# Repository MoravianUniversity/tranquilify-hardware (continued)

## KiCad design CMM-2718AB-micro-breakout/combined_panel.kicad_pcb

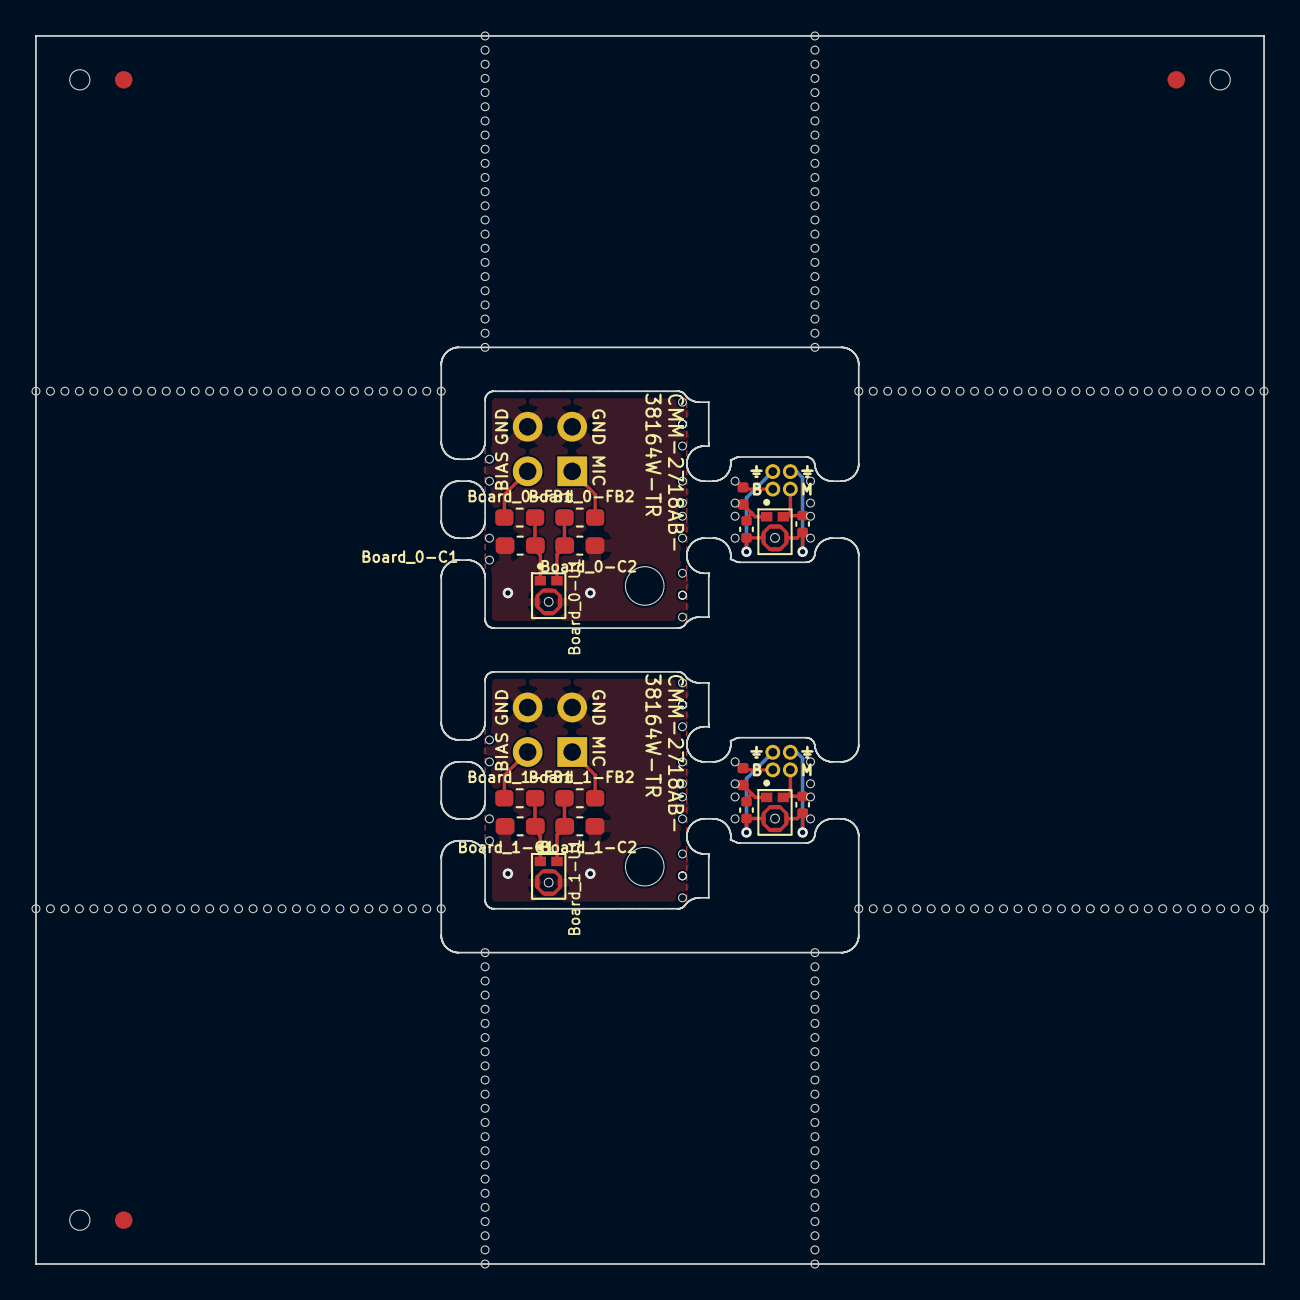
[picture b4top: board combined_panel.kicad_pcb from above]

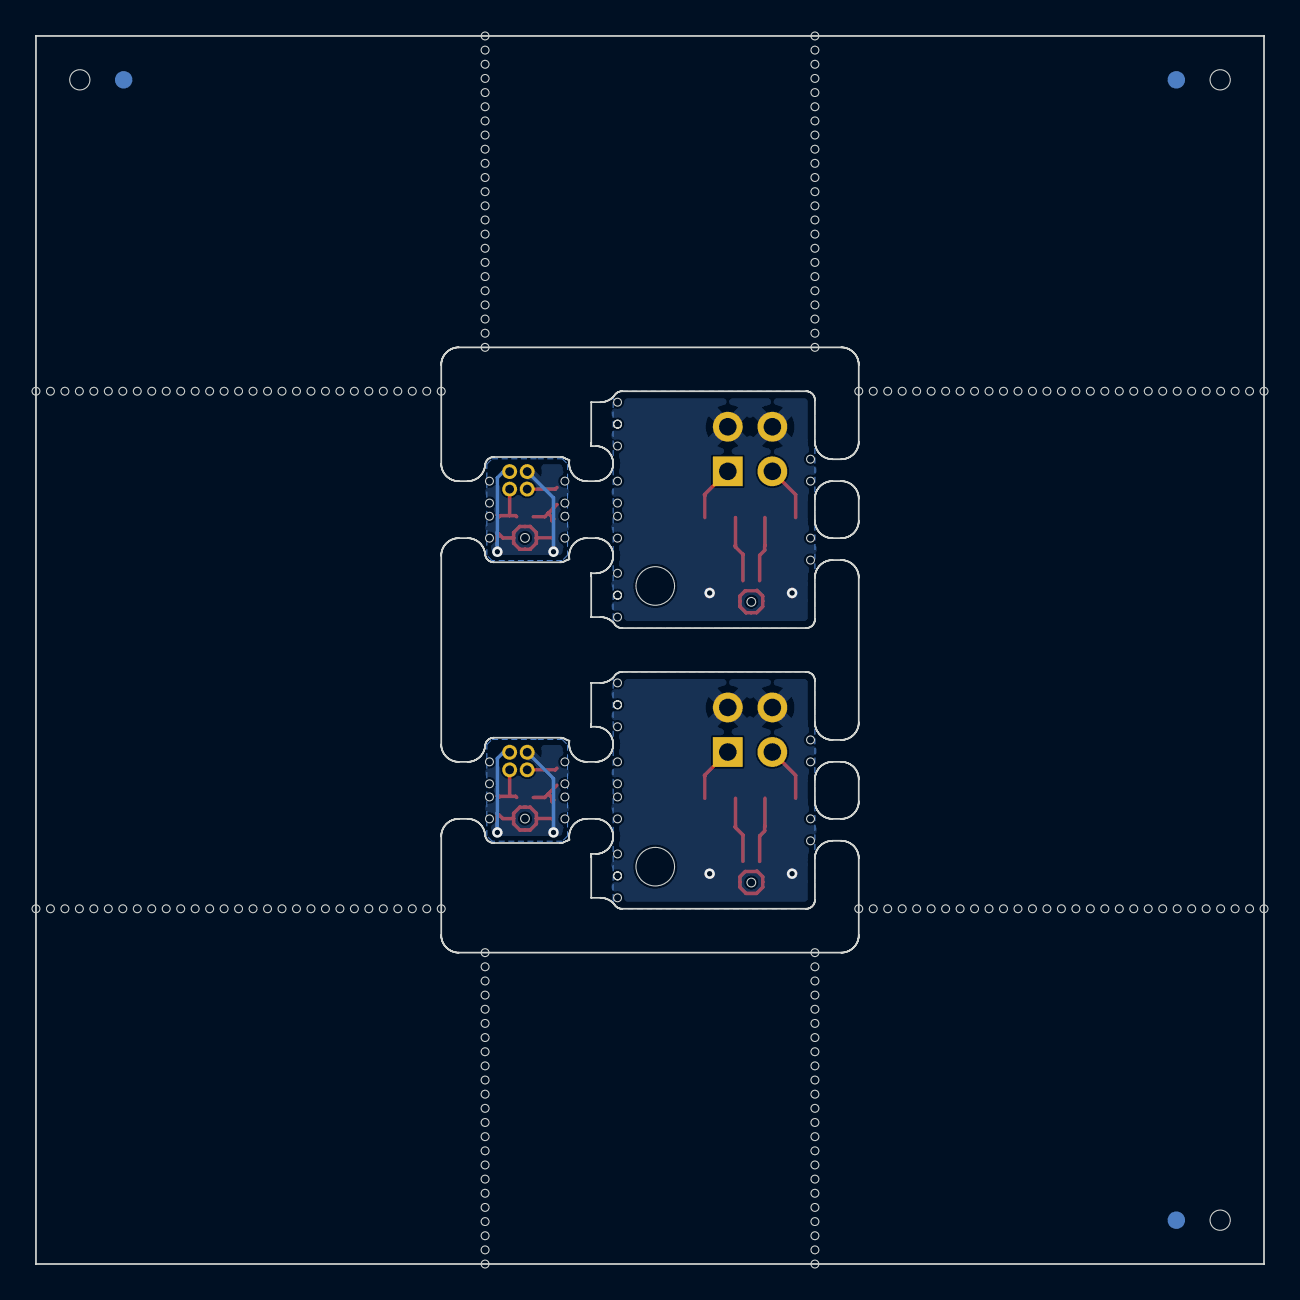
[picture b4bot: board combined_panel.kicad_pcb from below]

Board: 2 copper layers, 70.0 x 70.0 mm, 289 parts (3 on the bottom side), 18 nets.

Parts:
Board_0-C1, Board_1-C1: 100nF; C_0603_1608Metric_Pad1.08x0.95mm_HandSolder
Board_0-C2, Board_1-C2: 15pF; C_0603_1608Metric_Pad1.08x0.95mm_HandSolder
Board_0-FB1, Board_0-FB2, Board_1-FB1, Board_1-FB2: BLM18AG102SN1D; L_0603_1608Metric_Pad1.05x0.95mm_HandSolder
Board_0-H1, Board_1-H1: MountingHole_2.2mm_M2
Board_0-J1, Board_1-J1: Conn_02x02; PinHeader_2x02_P2.54mm_Vertical
Board_0-U1, Board_1-U1, Board_2-U1, Board_3-U1: CMM-2718AB-38164W-TR
Board_2-C1, Board_3-C1: 100nF; C_0402_1005Metric
Board_2-C2, Board_3-C2: 15pF; C_0402_1005Metric
Board_2-FB1, Board_3-FB1: BLM15AG102SN1D; L_0402_1005Metric
Board_2-J1, Board_3-J1: Conn; PinHeader_2x02_P1.00mm_Vertical
KiKit_FID_B_1, KiKit_FID_B_2, KiKit_FID_B_3: Fiducial
KiKit_FID_T_1, KiKit_FID_T_2, KiKit_FID_T_3: Fiducial
KiKit_MB_1_1, KiKit_MB_1_2, KiKit_MB_2_1, KiKit_MB_2_2, KiKit_MB_3_1, KiKit_MB_3_2, KiKit_MB_4_1, KiKit_MB_4_2, KiKit_MB_5_1, KiKit_MB_5_2, KiKit_MB_6_1, KiKit_MB_6_2, KiKit_MB_7_1, KiKit_MB_7_2, KiKit_MB_8_1, KiKit_MB_8_2, KiKit_MB_9_1, KiKit_MB_9_2, KiKit_MB_10_1, KiKit_MB_10_2, KiKit_MB_11_1, KiKit_MB_11_2, KiKit_MB_12_1, KiKit_MB_12_2, KiKit_MB_13_1, KiKit_MB_13_2, KiKit_MB_14_1, KiKit_MB_14_2, KiKit_MB_15_1, KiKit_MB_15_2, KiKit_MB_16_1, KiKit_MB_16_2, KiKit_MB_17_1, KiKit_MB_17_2, KiKit_MB_18_1, KiKit_MB_18_2, KiKit_MB_19_1, KiKit_MB_19_2, KiKit_MB_20_1, KiKit_MB_20_2, KiKit_MB_21_1, KiKit_MB_21_2, KiKit_MB_22_1, KiKit_MB_22_2, KiKit_MB_23_1, KiKit_MB_23_2, KiKit_MB_24_1, KiKit_MB_24_2, KiKit_MB_25_1, KiKit_MB_25_2, KiKit_MB_25_3, KiKit_MB_25_4, KiKit_MB_25_5, KiKit_MB_25_6, KiKit_MB_25_7, KiKit_MB_25_8, KiKit_MB_25_9, KiKit_MB_25_10, KiKit_MB_25_11, KiKit_MB_25_12, KiKit_MB_25_13, KiKit_MB_25_14, KiKit_MB_25_15, KiKit_MB_25_16, KiKit_MB_25_17, KiKit_MB_25_18, KiKit_MB_25_19, KiKit_MB_25_20, KiKit_MB_25_21, KiKit_MB_25_22, KiKit_MB_25_23, KiKit_MB_26_1, KiKit_MB_26_2, KiKit_MB_26_3, KiKit_MB_26_4, KiKit_MB_26_5, KiKit_MB_26_6, KiKit_MB_26_7, KiKit_MB_26_8, KiKit_MB_26_9, KiKit_MB_26_10, KiKit_MB_26_11, KiKit_MB_26_12, KiKit_MB_26_13, KiKit_MB_26_14, KiKit_MB_26_15, KiKit_MB_26_16, KiKit_MB_26_17, KiKit_MB_26_18, KiKit_MB_26_19, KiKit_MB_26_20, KiKit_MB_26_21, KiKit_MB_26_22, KiKit_MB_26_23, KiKit_MB_27_1, KiKit_MB_27_2, KiKit_MB_27_3, KiKit_MB_27_4, KiKit_MB_27_5, KiKit_MB_27_6, KiKit_MB_27_7, KiKit_MB_27_8, KiKit_MB_27_9, KiKit_MB_27_10, KiKit_MB_27_11, KiKit_MB_27_12, KiKit_MB_27_13, KiKit_MB_27_14, KiKit_MB_27_15, KiKit_MB_27_16, KiKit_MB_27_17, KiKit_MB_27_18, KiKit_MB_27_19, KiKit_MB_27_20, KiKit_MB_27_21, KiKit_MB_27_22, KiKit_MB_27_23, KiKit_MB_28_1, KiKit_MB_28_2, KiKit_MB_28_3, KiKit_MB_28_4, KiKit_MB_28_5, KiKit_MB_28_6, KiKit_MB_28_7, KiKit_MB_28_8, KiKit_MB_28_9, KiKit_MB_28_10, KiKit_MB_28_11, KiKit_MB_28_12, KiKit_MB_28_13, KiKit_MB_28_14, KiKit_MB_28_15, KiKit_MB_28_16, KiKit_MB_28_17, KiKit_MB_28_18, KiKit_MB_28_19, KiKit_MB_28_20, KiKit_MB_28_21, KiKit_MB_28_22, KiKit_MB_28_23, KiKit_MB_29_1, KiKit_MB_29_2, KiKit_MB_29_3, KiKit_MB_29_4, KiKit_MB_29_5, KiKit_MB_29_6, KiKit_MB_29_7, KiKit_MB_29_8, KiKit_MB_29_9, KiKit_MB_29_10, KiKit_MB_29_11, KiKit_MB_29_12, KiKit_MB_29_13, KiKit_MB_29_14, KiKit_MB_29_15, KiKit_MB_29_16, KiKit_MB_29_17, KiKit_MB_29_18, KiKit_MB_29_19, KiKit_MB_29_20, KiKit_MB_29_21, KiKit_MB_29_22, KiKit_MB_29_23, KiKit_MB_29_24, KiKit_MB_29_25, KiKit_MB_29_26, KiKit_MB_29_27, KiKit_MB_29_28, KiKit_MB_29_29, KiKit_MB_30_1, KiKit_MB_30_2, KiKit_MB_30_3, KiKit_MB_30_4, KiKit_MB_30_5, KiKit_MB_30_6, KiKit_MB_30_7, KiKit_MB_30_8, KiKit_MB_30_9, KiKit_MB_30_10, KiKit_MB_30_11, KiKit_MB_30_12, KiKit_MB_30_13, KiKit_MB_30_14, KiKit_MB_30_15, KiKit_MB_30_16, KiKit_MB_30_17, KiKit_MB_30_18, KiKit_MB_30_19, KiKit_MB_30_20, KiKit_MB_30_21, KiKit_MB_30_22, KiKit_MB_30_23, KiKit_MB_30_24, KiKit_MB_30_25, KiKit_MB_30_26, KiKit_MB_30_27, KiKit_MB_30_28, KiKit_MB_30_29, KiKit_MB_31_1, KiKit_MB_31_2, KiKit_MB_31_3, KiKit_MB_31_4, KiKit_MB_31_5, KiKit_MB_31_6, KiKit_MB_31_7, KiKit_MB_31_8, KiKit_MB_31_9, KiKit_MB_31_10, KiKit_MB_31_11, KiKit_MB_31_12, KiKit_MB_31_13, KiKit_MB_31_14, KiKit_MB_31_15, KiKit_MB_31_16, KiKit_MB_31_17, KiKit_MB_31_18, KiKit_MB_31_19, KiKit_MB_31_20, KiKit_MB_31_21, KiKit_MB_31_22, KiKit_MB_31_23, KiKit_MB_31_24, KiKit_MB_31_25, KiKit_MB_31_26, KiKit_MB_31_27, KiKit_MB_31_28, KiKit_MB_31_29, KiKit_MB_32_1, KiKit_MB_32_2, KiKit_MB_32_3, KiKit_MB_32_4, KiKit_MB_32_5, KiKit_MB_32_6, KiKit_MB_32_7, KiKit_MB_32_8, KiKit_MB_32_9, KiKit_MB_32_10, KiKit_MB_32_11, KiKit_MB_32_12, KiKit_MB_32_13, KiKit_MB_32_14, KiKit_MB_32_15, KiKit_MB_32_16, KiKit_MB_32_17, KiKit_MB_32_18, KiKit_MB_32_19, KiKit_MB_32_20, KiKit_MB_32_21, KiKit_MB_32_22, KiKit_MB_32_23, KiKit_MB_32_24, KiKit_MB_32_25, KiKit_MB_32_26, KiKit_MB_32_27, KiKit_MB_32_28, KiKit_MB_32_29: NPTH
KiKit_TO_1, KiKit_TO_2, KiKit_TO_3: NPTH

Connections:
Board_0-/BIAS: Board_0-FB1.1, Board_0-J1.3
Board_0-/OUT: Board_0-FB2.2, Board_0-J1.4
Board_0-/VDD: Board_0-C1.1, Board_0-FB1.2, Board_0-U1.1 (VDD)
Board_0-GND: Board_0-C1.2, Board_0-C2.2, Board_0-J1.1, Board_0-J1.2, Board_0-U1.3 (GND)
Board_0-Net-(U1-OUT): Board_0-C2.1, Board_0-FB2.1, Board_0-U1.2 (OUT)
Board_1-/BIAS: Board_1-FB1.1, Board_1-J1.3
Board_1-/OUT: Board_1-FB2.2, Board_1-J1.4
Board_1-/VDD: Board_1-C1.1, Board_1-FB1.2, Board_1-U1.1 (VDD)
Board_1-GND: Board_1-C1.2, Board_1-C2.2, Board_1-J1.1, Board_1-J1.2, Board_1-U1.3 (GND)
Board_1-Net-(U1-OUT): Board_1-C2.1, Board_1-FB2.1, Board_1-U1.2 (OUT)
Board_2-/BIAS: Board_2-FB1.1, Board_2-J1.3
Board_2-/OUT: Board_2-C2.1, Board_2-J1.4, Board_2-U1.2 (OUT)
Board_2-/VDD: Board_2-C1.1, Board_2-FB1.2, Board_2-U1.1 (VDD)
Board_2-GND: Board_2-C1.2, Board_2-C2.2, Board_2-J1.1, Board_2-J1.2, Board_2-U1.3 (GND)
Board_3-/BIAS: Board_3-FB1.1, Board_3-J1.3
Board_3-/OUT: Board_3-C2.1, Board_3-J1.4, Board_3-U1.2 (OUT)
Board_3-/VDD: Board_3-C1.1, Board_3-FB1.2, Board_3-U1.1 (VDD)
Board_3-GND: Board_3-C1.2, Board_3-C2.2, Board_3-J1.1, Board_3-J1.2, Board_3-U1.3 (GND)

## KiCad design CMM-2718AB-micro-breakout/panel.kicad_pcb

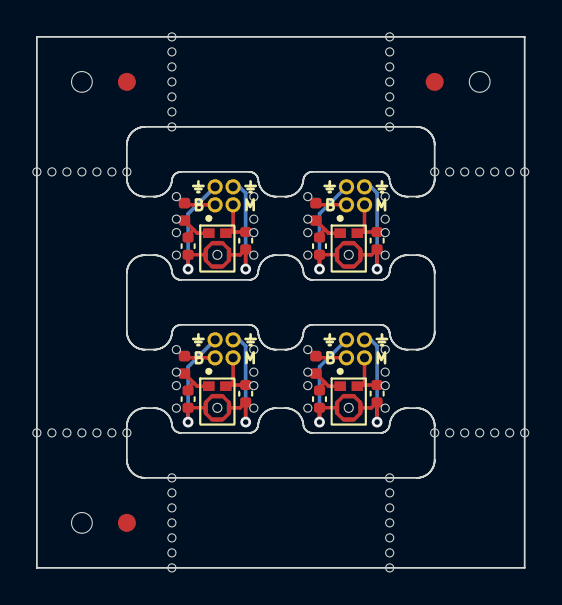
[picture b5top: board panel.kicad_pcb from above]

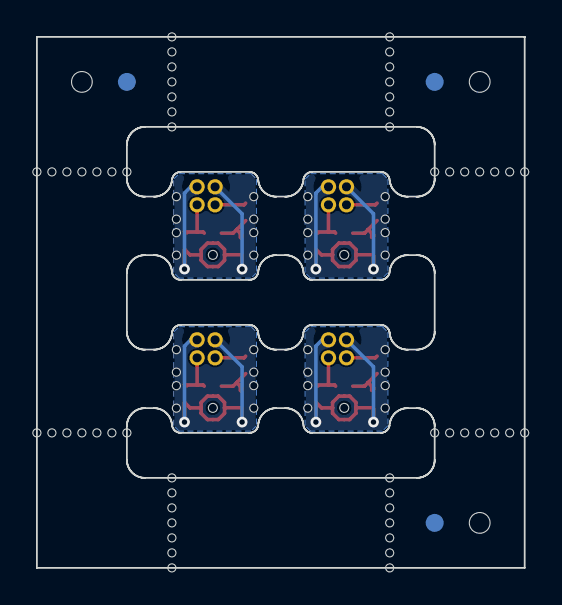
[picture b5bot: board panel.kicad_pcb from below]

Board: 2 copper layers, 27.1 x 29.5 mm, 117 parts (3 on the bottom side), 16 nets.

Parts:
C1, C1#2, C1#3, C1#4: 100nF; C_0402_1005Metric
C2, C2#2, C2#3, C2#4: 15pF; C_0402_1005Metric
FB1, FB1#2, FB1#3, FB1#4: BLM15AG102SN1D; L_0402_1005Metric
J1, J1#2, J1#3, J1#4: Conn; PinHeader_2x02_P1.00mm_Vertical
KiKit_FID_B_1, KiKit_FID_B_2, KiKit_FID_B_3: Fiducial
KiKit_FID_T_1, KiKit_FID_T_2, KiKit_FID_T_3: Fiducial
KiKit_MB_1_1, KiKit_MB_1_2, KiKit_MB_2_1, KiKit_MB_2_2, KiKit_MB_3_1, KiKit_MB_3_2, KiKit_MB_4_1, KiKit_MB_4_2, KiKit_MB_5_1, KiKit_MB_5_2, KiKit_MB_6_1, KiKit_MB_6_2, KiKit_MB_7_1, KiKit_MB_7_2, KiKit_MB_8_1, KiKit_MB_8_2, KiKit_MB_9_1, KiKit_MB_9_2, KiKit_MB_10_1, KiKit_MB_10_2, KiKit_MB_11_1, KiKit_MB_11_2, KiKit_MB_12_1, KiKit_MB_12_2, KiKit_MB_13_1, KiKit_MB_13_2, KiKit_MB_14_1, KiKit_MB_14_2, KiKit_MB_15_1, KiKit_MB_15_2, KiKit_MB_16_1, KiKit_MB_16_2, KiKit_MB_17_1, KiKit_MB_17_2, KiKit_MB_17_3, KiKit_MB_17_4, KiKit_MB_17_5, KiKit_MB_17_6, KiKit_MB_17_7, KiKit_MB_18_1, KiKit_MB_18_2, KiKit_MB_18_3, KiKit_MB_18_4, KiKit_MB_18_5, KiKit_MB_18_6, KiKit_MB_18_7, KiKit_MB_19_1, KiKit_MB_19_2, KiKit_MB_19_3, KiKit_MB_19_4, KiKit_MB_19_5, KiKit_MB_19_6, KiKit_MB_19_7, KiKit_MB_20_1, KiKit_MB_20_2, KiKit_MB_20_3, KiKit_MB_20_4, KiKit_MB_20_5, KiKit_MB_20_6, KiKit_MB_20_7, KiKit_MB_21_1, KiKit_MB_21_2, KiKit_MB_21_3, KiKit_MB_21_4, KiKit_MB_21_5, KiKit_MB_21_6, KiKit_MB_21_7, KiKit_MB_22_1, KiKit_MB_22_2, KiKit_MB_22_3, KiKit_MB_22_4, KiKit_MB_22_5, KiKit_MB_22_6, KiKit_MB_22_7, KiKit_MB_23_1, KiKit_MB_23_2, KiKit_MB_23_3, KiKit_MB_23_4, KiKit_MB_23_5, KiKit_MB_23_6, KiKit_MB_23_7, KiKit_MB_24_1, KiKit_MB_24_2, KiKit_MB_24_3, KiKit_MB_24_4, KiKit_MB_24_5, KiKit_MB_24_6, KiKit_MB_24_7: NPTH
KiKit_TO_1, KiKit_TO_2, KiKit_TO_3: NPTH
U1, U1#2, U1#3, U1#4: CMM-2718AB-38164W-TR

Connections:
Board_0-/BIAS: FB1#3.1, J1.3
Board_0-/OUT: C2#2.1, J1.4, U1.2 (OUT)
Board_0-/VDD: C1#2.1, FB1#3.2, U1.1 (VDD)
Board_0-GND: C1#2.2, C2#2.2, J1.1, J1.2, U1.3 (GND)
Board_1-/BIAS: FB1.1, J1#2.3
Board_1-/OUT: C2#4.1, J1#2.4, U1#4.2 (OUT)
Board_1-/VDD: C1#4.1, FB1.2, U1#4.1 (VDD)
Board_1-GND: C1#4.2, C2#4.2, J1#2.1, J1#2.2, U1#4.3 (GND)
Board_2-/BIAS: FB1#4.1, J1#4.3
Board_2-/OUT: C2.1, J1#4.4, U1#2.2 (OUT)
Board_2-/VDD: C1.1, FB1#4.2, U1#2.1 (VDD)
Board_2-GND: C1.2, C2.2, J1#4.1, J1#4.2, U1#2.3 (GND)
Board_3-/BIAS: FB1#2.1, J1#3.3
Board_3-/OUT: C2#3.1, J1#3.4, U1#3.2 (OUT)
Board_3-/VDD: C1#3.1, FB1#2.2, U1#3.1 (VDD)
Board_3-GND: C1#3.2, C2#3.2, J1#3.1, J1#3.2, U1#3.3 (GND)

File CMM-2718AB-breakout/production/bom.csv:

Designator,Footprint,Quantity,Value,LCSC Part #
C1,0603,1,100nF,C108079
C2,0603,1,15pF,C107037
"FB1, FB2",0603,2,BLM18AG102SN1D,C85824
U1,CMM-2718AB-38164W-TR,1,CMM-2718AB-38164W-TR,C7497787
